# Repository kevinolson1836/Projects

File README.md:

# Kevin's Lab

A VSCode-style site for browsing engineering projects and build logs. Built with **Astro**.

## Requirements

- **Node.js** >= 18.14.1 (recommended: 20.x or 22.x)
- npm

## Setup

```bash
npm install
```

## Development

```bash
npm run dev
```

Open [http://localhost:4321](http://localhost:4321).

## Build

```bash
npm run build
```

Output in `dist/`.

## Project structure

- **Dashboard** (`/`) – stats and active projects
- **Project pages** (`/projects/[slug]`) – build logs (Markdown) with code highlighting

Add projects by creating folders under `projects/`:

```
projects/
  your-project/
    project.yaml   # slug, title, status, progress, started, tags
    notes.md       # Markdown build log
```

### Embedding images

Images in `notes.md` are supported. Put image files in **`public/images/{project-slug}/`** and reference them with a relative path in Markdown:

```markdown

```

- **Relative path** `./photo.png` is resolved to `/images/{project-slug}/photo.png` (so the file must be in `public/images/{project-slug}/photo.png`).
- **Absolute path** `/images/...` works as-is.

### Work sidebar

The activity bar has two views: **Explorer** (project files) and **Work** (work-related links). Edit `src/lib/work.ts` to add or change Work items (e.g. Notion, GitHub, Figma). Use `external: true` and a full URL for links that open in a new tab.

## Tech

- Astro (static)
- marked + highlight.js (Markdown + syntax highlighting)
- js-yaml (project metadata)

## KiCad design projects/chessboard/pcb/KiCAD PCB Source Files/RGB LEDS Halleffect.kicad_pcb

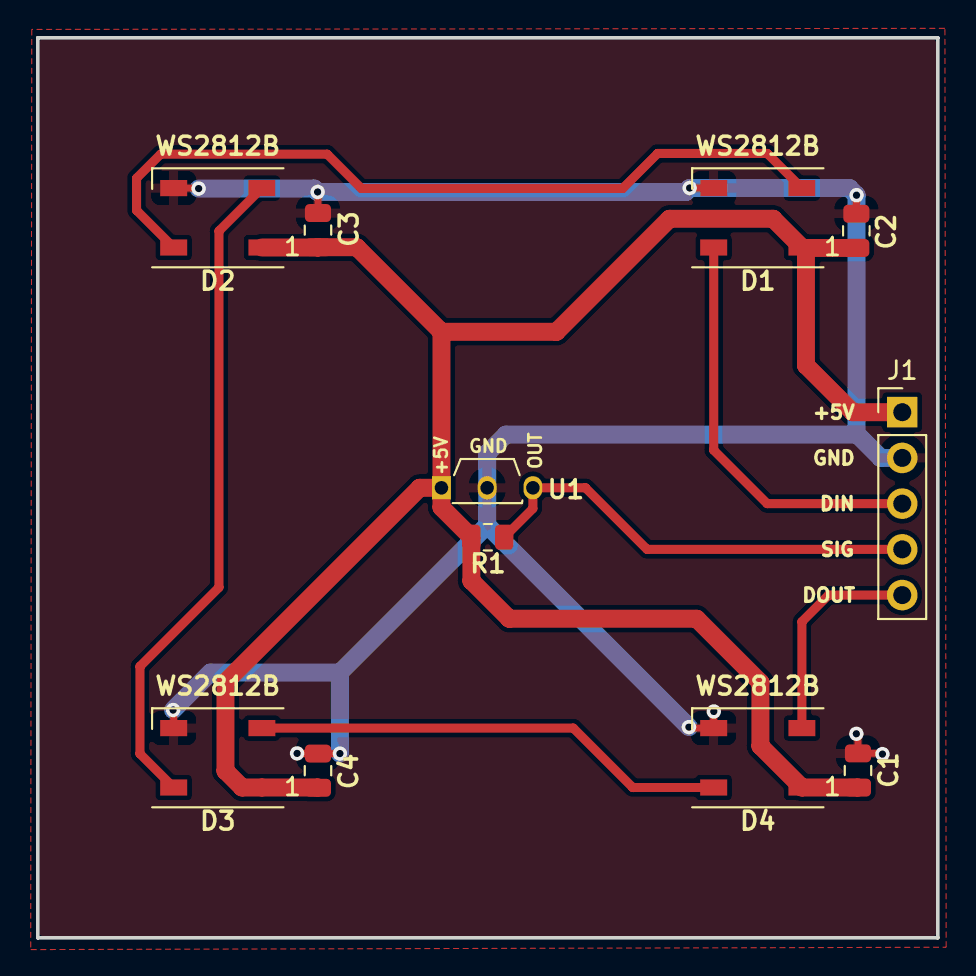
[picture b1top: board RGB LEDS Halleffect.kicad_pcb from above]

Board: 2 copper layers, 50.0 x 50.0 mm, 11 parts (0 on the bottom side), 8 nets.

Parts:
C1, C2, C3, C4: 100nF; C_0805_2012Metric
D1, D2, D3, D4: WS2812B; LED_WS2812B_PLCC4_5.0x5.0mm_P3.2mm
J1: Screw_Terminal_01x05; PinHeader_1x05_P2.54mm_Vertical
R1: 10k; R_0805_2012Metric
U1: A3144; TO-92S_Wide

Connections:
+5V: C1.2, C2.2, C3.2, C4.2, D1.1 (VDD), D2.1 (VDD), D3.1 (VDD), D4.1 (VDD), J1.1, R1.1, U1.1 (VCC)
GND: C1.1, C2.1, C3.1, C4.1, D1.3 (VSS), D2.3 (VSS), D3.3 (VSS), D4.3 (VSS), J1.2, U1.2 (GND)
unnamed: D1.2 (DOUT), D2.4 (DIN)
unnamed: D2.2 (DOUT), D3.4 (DIN)
unnamed: D3.2 (DOUT), D4.4 (DIN)
RGB_Din: D1.4 (DIN), J1.3
RGB_Dout: D4.2 (DOUT), J1.5
Sensor_Out: J1.4, R1.2, U1.3 (VOUT)

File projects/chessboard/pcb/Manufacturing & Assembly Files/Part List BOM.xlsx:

Item | Qty | Reference(s) | Value | LibPart | Footprint | LCSC Part#
1 | 4 | C1, C2, C3, C4 | 100nF | Device:C_Small | Ahsan Libs:C_0805_2012Metric | C49678
2 | 4 | D1, D2, D3, D4 | WS2812B | LED:WS2812B | LED_SMD:LED_WS2812B_PLCC4_5.0x5.0mm_P3.2mm | C114586
3 | 1 | J1 | OUT | Connector:Screw_Terminal_01x05 | Connector_PinHeader_2.54mm:PinHeader_1x05_P2.54mm_Vertical
4 | 1 | R1 | 10k | Device:R | Ahsan Libs:R_0805_2012Metric | C17414
5 | 1 | U1 | A3144 | Sensor_Magnetic:A1302KUA-T | PCM_Package_TO_SOT_THT_AKL:TO-92S_Wide | C558879

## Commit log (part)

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2026-03-12 inital start
2026-03-12 small edits and jukebox write up
2026-03-13 updated site funconalioty
2026-03-14 jukebox
2026-03-14 yeah
2026-03-14 added more projects
2026-03-15 chess
2026-03-17 added todo
2026-03-18 example
2026-03-21 idkd man
2026-03-22 work stuff
2026-03-24 ideas poage
2026-03-24 work updtes
2026-04-04 yupo
2026-04-04 vault backup: 2026-04-04 16:31:00
